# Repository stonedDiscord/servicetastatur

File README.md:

# Servicetastatur

Ein Nachbau der Servicetastatur für Merkur Geräte ab Profitech 3000.

Man kann diese bei Auftragsfertigern bauen lassen,
EPROM, CPU, Display und Gehäuse müssen seperat beschafft werden.

Gehäuse ist [in Arbeit](https://github.com/stonedDiscord/servicetastatur/blob/master/case.scad),
es werden die Bibliotheken [jl_scad](https://github.com/lijon/jl_scad) und [BOSL2](https://github.com/BelfrySCAD/BOSL2) benötigt.

## Lizenz

Nachbauen und Modifizieren durch Dritte ist erlaubt, die Dokumentation inkl Schaltplan und Gerber müssen aber mit weitergegeben werden.
Die Lizenz gibt es hier auf Deutsch
https://creativecommons.org/licenses/by-sa/4.0/deed.de

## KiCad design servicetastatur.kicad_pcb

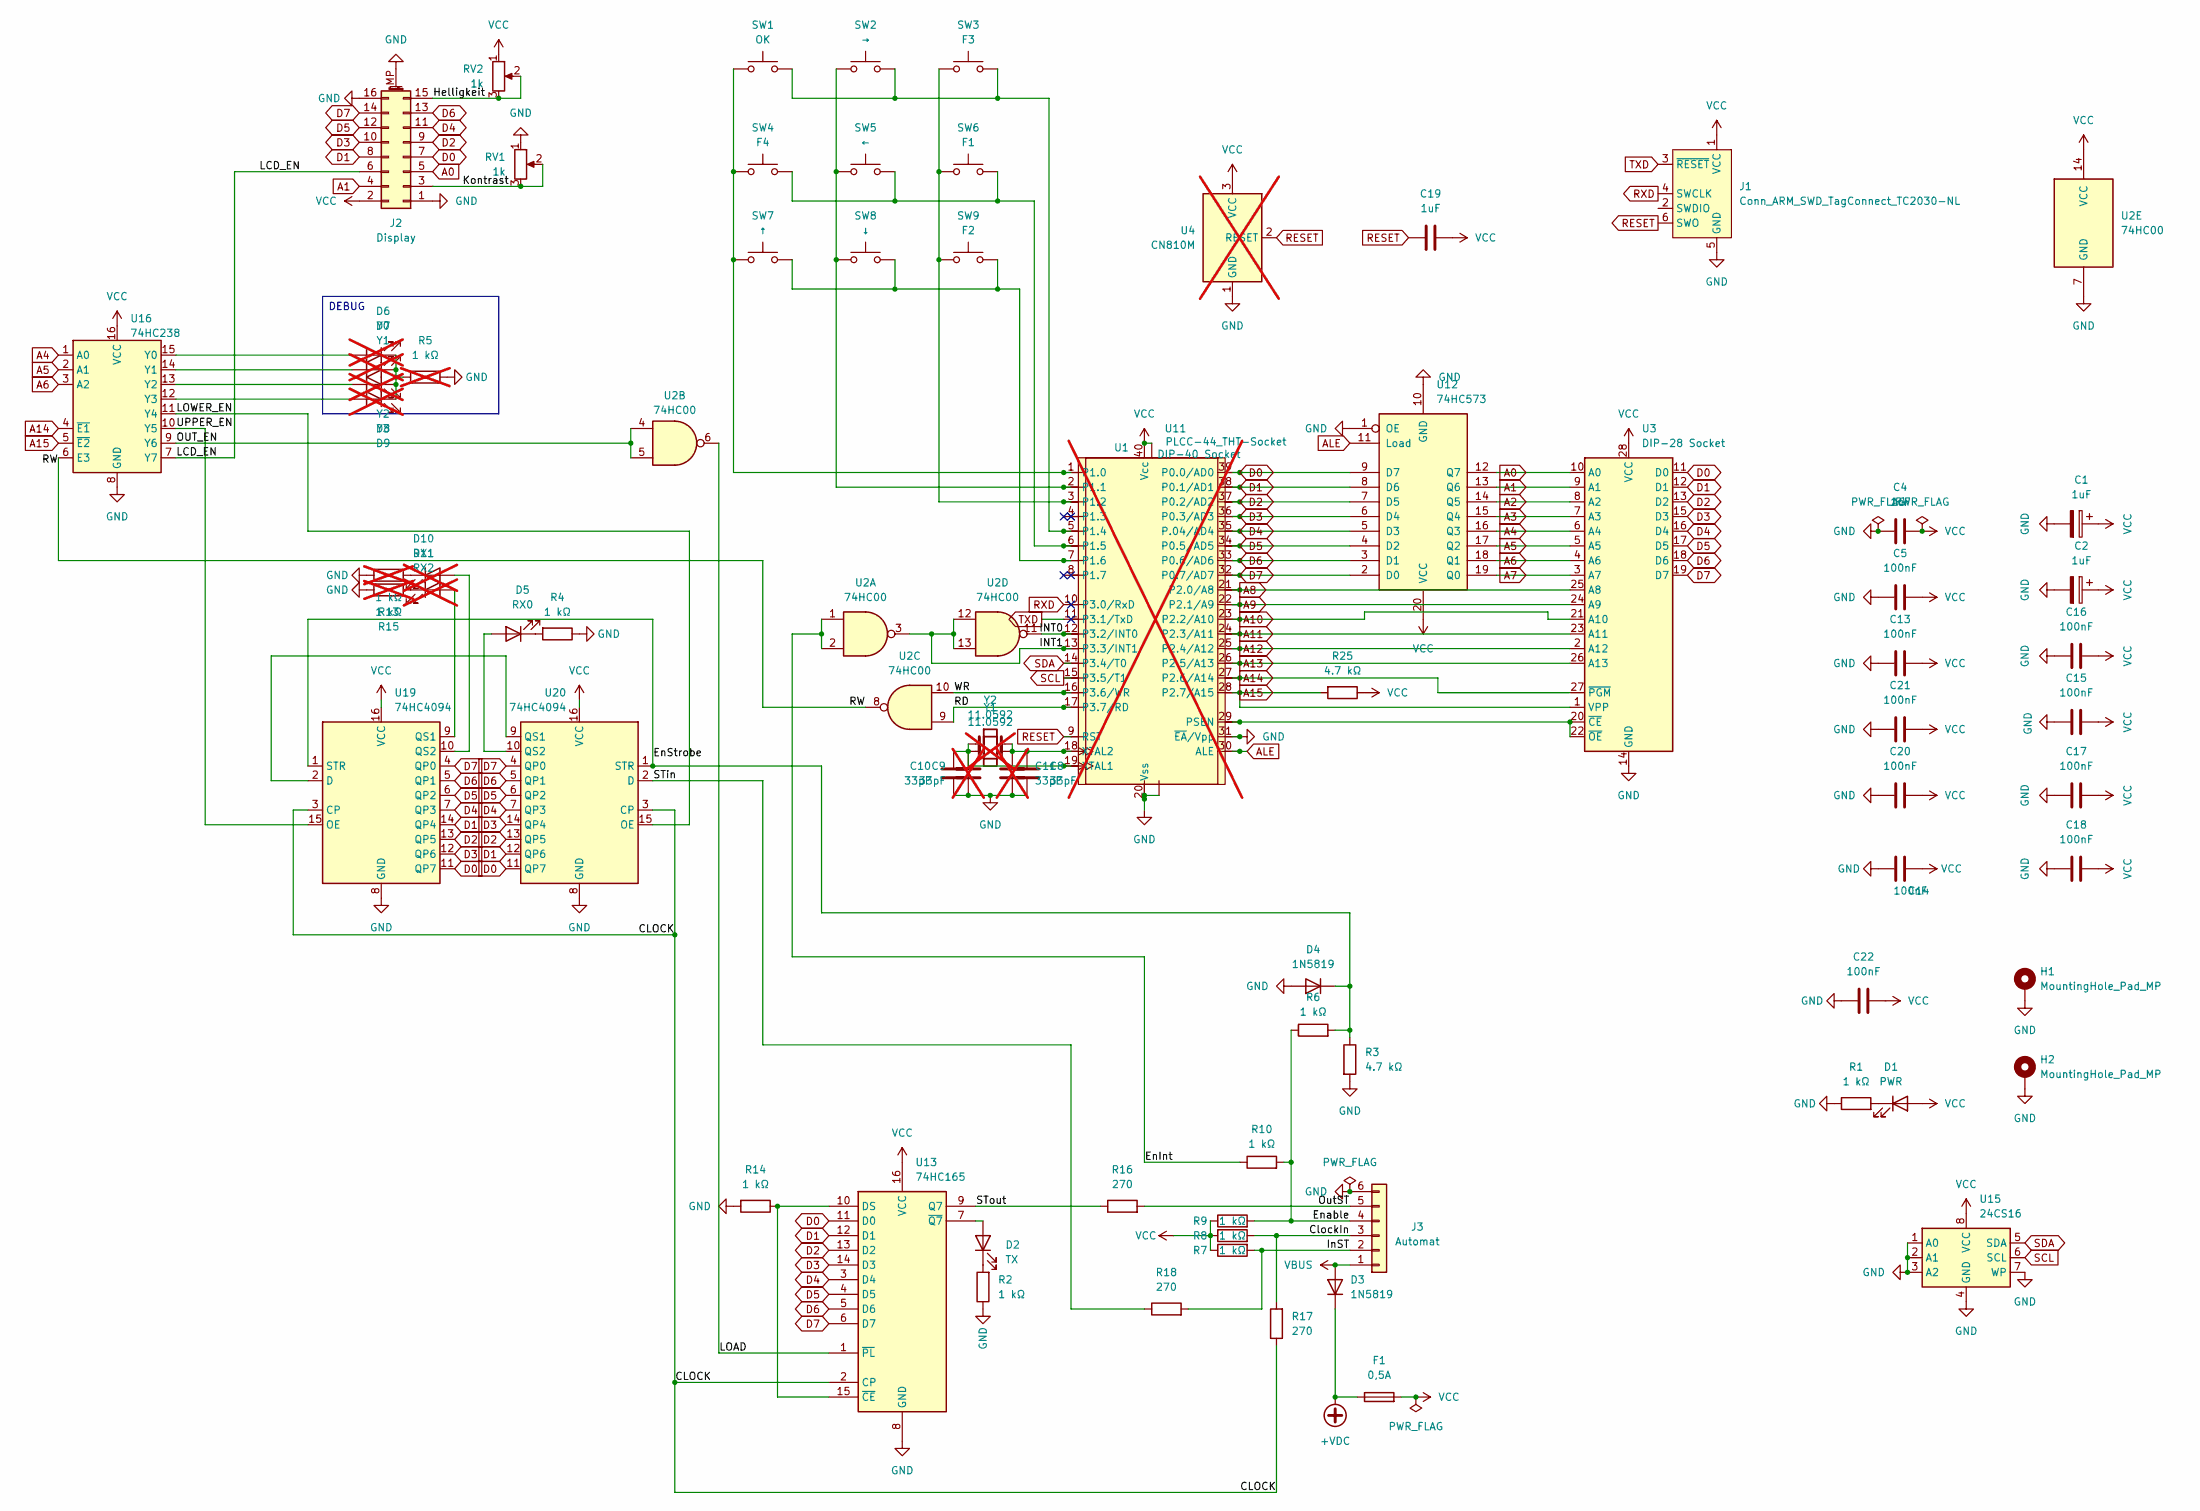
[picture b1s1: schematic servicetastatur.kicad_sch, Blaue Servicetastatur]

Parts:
C1, C2, C4, C19: 1uF; C_1206_3216Metric
C5, C13, C14, C15, C16, C17, C18, C20, C21, C22: 100nF; C_0603_1608Metric
C8, C10: 33pF; C_0603_1608Metric
C9, C11: 33pF; C_0603_1608Metric; not fitted
D1: PWR; LED_0805_2012Metric
D2: TX; LED_0805_2012Metric
D3, D4: 1N5819; D_SOD-123
D5: RX0; LED_0805_2012Metric
D6: Y0; LED_0805_2012Metric; not fitted
D7: Y1; LED_0805_2012Metric; not fitted
D8: Y2; LED_0805_2012Metric; not fitted
D9: Y3; LED_0805_2012Metric; not fitted
D10: RX1; LED_0805_2012Metric; not fitted
D11: RX2; LED_0805_2012Metric; not fitted
F1: 0,5A; Fuse_0805_2012Metric
H1, H2: MountingHole_Pad_MP; MountingHole 3.5mm
J1: Conn_ARM_SWD_TagConnect_TC2030-NL; Tag-Connect_TC2030-IDC-NL_2x03_P1.27mm_Vertical
J2: Display; LCDdisplay
J3: Automat; Conn01x06
R1, R2, R4, R6, R7, R8, R9, R10, R14: 1 kΩ; R_0603_1608Metric
R3, R25: 4.7 kΩ; R_0603_1608Metric
R5, R13, R15: 1 kΩ; R_0603_1608Metric; not fitted
R16, R17, R18: 270; R_0603_1608Metric
RV1, RV2: 1k; Potentiometer_Piher_PT-6-V_Vertical_Hole
SW1: OK; SW_Push_1P1T_XKB_TS-1187A
SW2: →; SW_Push_1P1T_XKB_TS-1187A
SW3: F3; SW_Push_1P1T_XKB_TS-1187A
SW4: F4; SW_Push_1P1T_XKB_TS-1187A
SW5: ←; SW_Push_1P1T_XKB_TS-1187A
SW6: F1; SW_Push_1P1T_XKB_TS-1187A
SW7: ↑; SW_Push_1P1T_XKB_TS-1187A
SW8: ↓; SW_Push_1P1T_XKB_TS-1187A
SW9: F2; SW_Push_1P1T_XKB_TS-1187A
U1: DIP-40 Socket; DIP-40_W15.24mm
U2: 74HC00; SOIC-14_3.9x8.7mm_P1.27mm
U3: DIP-28 Socket; DIP-28_W15.24mm
U4: CN810M; SOT-23; not fitted
U11: PLCC-44_THT-Socket; not fitted
U12: 74HC573; TSSOP-20_4.4x6.5mm_P0.65mm
U13: 74HC165; SOP-16_4.4x10.4mm_P1.27mm
U15: 24CS16; SO-8_3.9x4.9mm_P1.27mm
U16: 74HC238; SOIC-16W_5.3x10.2mm_P1.27mm
U19, U20: 74HC4094; SOIC-16W_5.3x10.2mm_P1.27mm
Y1: 11.0592; Crystal_HC49-U_Vertical; not fitted
Y2: 11.0592; Crystal_SMD_HC49-SD

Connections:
+VDC: D3.1 (K), F1.1
/CLOCK: R17.1, U13.2 (CP), U19.3 (CP), U20.3 (CP)
/ClockIn: J3.3, R8.2, R17.2
/EnInt: R10.1, U2.1, U2.2
/EnStrobe: D4.1 (K), R3.1, R6.2, U19.1 (STR), U20.1 (STR)
/Enable: J3.4, R6.1, R9.2, R10.2
/Helligkeit: J2.15, RV2.2, RV2.3
/INT0: U1.12 (P3.2/INT0), U2.11, U11.14 (P3.2/INT0)
/INT1: U1.13 (P3.3/INT1), U2.3, U2.12, U2.13, U11.15 (P3.3/INT1)
/InST: J3.2, R7.2, R18.2
/Kontrast: J2.3, RV1.2, RV1.3
/LCD_EN: J2.6, U16.7 (Y7)
/LOAD: U2.6, U13.1 (~PL)
/LOWER_EN: U16.11 (Y4), U20.15 (OE)
/OUT_EN: U2.4, U2.5, U16.9 (Y6)
/OutST: J3.5, R16.2
/RD: U1.17 (P3.7/RD), U2.9, U11.19 (P3.7/RD)
/RW: U2.8, U16.6 (E3)
/STin: R18.1, U20.2 (D)
/STout: R16.1, U13.9 (Q7)
/UPPER_EN: U16.10 (Y5), U19.15 (OE)
/WR: U1.16 (P3.6/WR), U2.10, U11.18 (P3.6/WR)
A0: J2.5, U3.10 (A0), U12.12 (Q7)
A1: J2.4, U3.9 (A1), U12.13 (Q6)
A2: U3.8 (A2), U12.14 (Q5)
A3: U3.7 (A3), U12.15 (Q4)
A4: U3.6 (A4), U12.16 (Q3), U16.1 (A0)
A5: U3.5 (A5), U12.17 (Q2), U16.2 (A1)
A6: U3.4 (A6), U12.18 (Q1), U16.3 (A2)
A7: U3.3 (A7), U12.19 (Q0)
A8: U1.21 (P2.0/A8), U3.25 (A8), U11.24 (P2.0/A8)
A9: U1.22 (P2.1/A9), U3.24 (A9), U11.25 (P2.1/A9)
A10: U1.23 (P2.2/A10), U3.21 (A10), U11.26 (P2.2/A10)
A11: U1.24 (P2.3/A11), U3.23 (A11), U11.27 (P2.3/A11)
A12: U1.25 (P2.4/A12), U3.2 (A12), U11.28 (P2.4/A12)
A13: U1.26 (P2.5/A13), U3.26 (A13), U11.29 (P2.5/A13)
A14: U1.27 (P2.6/A14), U3.27 (~PGM), U11.30 (P2.6/A14), U16.4 (~E1)
A15: R25.2, U1.28 (P2.7/A15), U3.1 (VPP), U11.31 (P2.7/A15), U11.34 (NIC), U16.5 (~E2)
ALE: U1.30 (ALE), U11.33 (ALE), U12.11 (Load)
D0: J2.7, U1.39 (P0.0/AD0), U3.11 (D0), U11.43 (P0.0/AD0), U12.9 (D7), U13.11 (D0), U19.11 (QP7), U20.11 (QP7)
D1: J2.8, U1.38 (P0.1/AD1), U3.12 (D1), U11.42 (P0.1/AD1), U12.8 (D6), U13.12 (D1), U19.14 (QP4), U20.12 (QP6)
D2: J2.9, U1.37 (P0.2/AD2), U3.13 (D2), U11.41 (P0.2/AD2), U12.7 (D5), U13.13 (D2), U19.13 (QP5), U20.13 (QP5)
D3: J2.10, U1.36 (P0.3/AD3), U3.15 (D3), U11.40 (P0.3/AD3), U12.6 (D4), U13.14 (D3), U19.12 (QP6), U20.14 (QP4)
D4: J2.11, U1.35 (P.04/AD4), U3.16 (D4), U11.39 (P.04/AD4), U12.5 (D3), U13.3 (D4), U19.7 (QP3), U20.7 (QP3)
D5: J2.12, U1.34 (P0.5/AD5), U3.17 (D5), U11.38 (P0.5/AD5), U12.4 (D2), U13.4 (D5), U19.6 (QP2), U20.6 (QP2)
D6: J2.13, U1.33 (P0.6/AD6), U3.18 (D6), U11.37 (P0.6/AD6), U12.3 (D1), U13.5 (D6), U19.5 (QP1), U20.5 (QP1)
D7: J2.14, U1.32 (P0.7/AD7), U3.19 (D7), U11.36 (P0.7/AD7), U12.2 (D0), U13.6 (D7), U19.4 (QP0), U20.4 (QP0)
GND: C1.2, C2.2, C4.1, C5.1, C8.1, C9.1, C10.1, C11.1, C13.1, C14.2, C15.1, C16.1, C17.1, C18.1, C20.2, C21.2, C22.1, D4.2 (A), H1.MP, H2.MP, J1.5 (GND), J2.1, J2.16, J2.MP (MountPin), J3.6, R1.1, R2.1, R3.2, R4.1, R5.1, R13.1, R14.2, R15.1, RV1.1, U1.20 (Vss), U1.31 (~EA/Vpp), U2.7 (GND), U3.14 (GND), U4.1 (GND), U11.1 (Vss1), U11.22 (Vss), U11.35 (EA), U12.1 (OE), U12.10 (GND), U13.8 (GND), U15.1 (A0), U15.2 (A1), U15.3 (A2), U15.4 (GND), U15.7 (WP), U16.8 (GND), U19.8 (GND), U20.8 (GND)
unnamed: D1.1 (K), R1.2
unnamed: D2.2 (A), U13.7 (~Q7)
unnamed: D2.1 (K), R2.2
unnamed: D5.2 (A), U20.10 (QS2)
unnamed: D5.1 (K), R4.2
unnamed: D6.2 (A), U16.15 (Y0)
unnamed: D6.1 (K), D7.1 (K), D8.1 (K), D9.1 (K), R5.2
unnamed: D7.2 (A), U16.14 (Y1)
unnamed: D8.2 (A), U16.13 (Y2)
unnamed: D9.2 (A), U16.12 (Y3)
unnamed: D10.2 (A), U19.10 (QS2)
unnamed: D10.1 (K), R13.2
unnamed: D11.2 (A), U19.9 (QS1)
unnamed: D11.1 (K), R15.2
unnamed: SW1.1, SW4.1, SW7.1, U1.1 (P1.0), U11.2 (P1.0)
unnamed: SW2.1, SW5.1, SW8.1, U1.2 (P1.1), U11.3 (P1.1)
unnamed: SW3.1, SW6.1, SW9.1, U1.3 (P1.2), U11.4 (P1.2)
unnamed: SW1.2, SW2.2, SW3.2, U1.5 (P1.4), U11.6 (P1.4)
unnamed: SW4.2, SW5.2, SW6.2, U1.6 (P1.5), U11.7 (P1.5)
unnamed: SW7.2, SW8.2, SW9.2, U1.7 (P1.6), U11.8 (P1.6)
unnamed: U1.29 (PSEN), U3.20 (~CE), U3.22 (~OE), U11.32 (PSEN)
unnamed: C9.2, C10.2, U1.19 (XTAL1), U11.21 (XTAL1), Y1.1, Y2.1
unnamed: C8.2, C11.2, U1.18 (XTAL2), U11.20 (XTAL2), Y1.2, Y2.2
unnamed: R14.1, U13.10 (DS), U13.15 (~CE)
unnamed: U19.2 (D), U20.9 (QS1)
RESET: C19.1, J1.6 (SWO), U1.9 (RST), U4.2 (RESET), U11.10 (RST)
RXD: J1.4 (SWCLK), U1.10 (P3.0/RxD)
SCL: U1.15 (P3.5/T1), U11.17 (P3.5/T1), U15.6 (SCL)
SDA: U1.14 (P3.4/T0), U11.16 (P3.4/T0), U15.5 (SDA)
TXD: J1.3 (~RESET), U1.11 (P3.1/TxD)
VBUS: D3.2 (A), J3.1
VCC: C1.1, C2.1, C4.2, C5.2, C13.2, C14.1, C15.2, C16.2, C17.2, C18.2, C19.2, C20.1, C21.1, C22.2, D1.2 (A), F1.2, J1.1 (VCC), J2.2, R7.1, R8.1, R9.1, R25.1, RV2.1, U1.40 (Vcc), U2.14 (VCC), U3.28 (VCC), U4.3 (VCC), U11.44 (Vcc), U12.20 (VCC), U13.16 (VCC), U15.8 (VCC), U16.16 (VCC), U19.16 (VCC), U20.16 (VCC)

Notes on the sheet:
DEBUG

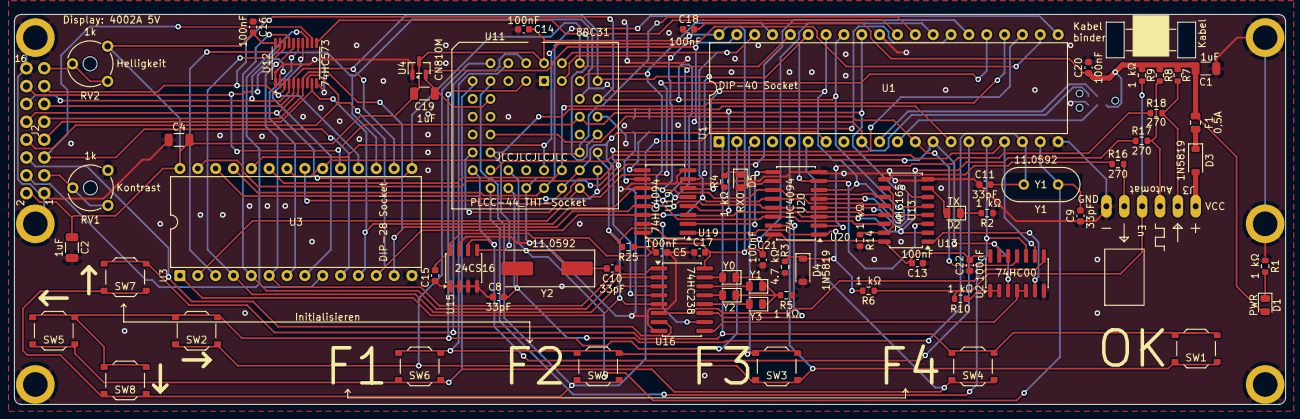
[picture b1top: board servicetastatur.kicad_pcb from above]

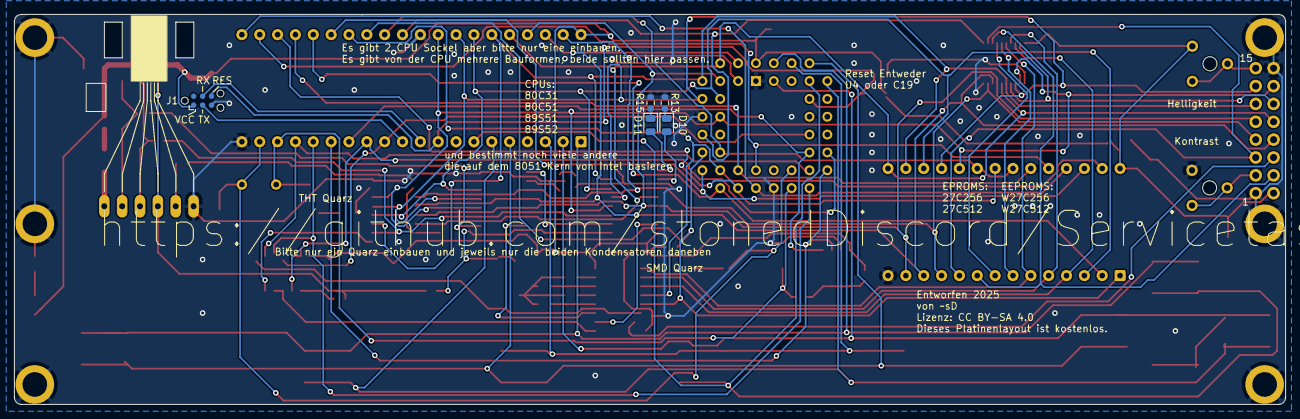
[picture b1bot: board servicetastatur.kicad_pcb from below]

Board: 2 copper layers, 180.9 x 55.5 mm, 76 parts (5 on the bottom side), 80 nets.

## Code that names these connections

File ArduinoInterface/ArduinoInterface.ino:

// Servicetastatur-Interface
// J3 (top to bottom): VBUS - InST - ClockIn - Enable - STout - GND
// TX (Board to Machine): U13 74HC165 (8-bit PISO, no swap, no pin reversal)
// RX (Machine to Board): U20+U19 74HC4094 Cascade (16-bit SIPO, swap D1/D3 on U19, pins reversed QP7=D0)

const int PIN_TX  = 5;  // Arduino Output: InST / 2STin at U20 (Board RX)
const int PIN_EN  = 2;  // Arduino Input: EnStrobe from machine (INT0)
const int PIN_CLK = 3;  // Arduino Input: Clock from machine (INT1)
const int PIN_RX  = 4;  // Arduino Input: STout from U13 (Board TX)

// TX from board perspective (sniffed by Arduino from U13)
volatile uint16_t txShift   = 0;
volatile uint16_t txLatched = 0;
volatile bool     txReady   = false;

// RX from board perspective (driven by Arduino into U20/U19)
volatile uint16_t rxData   = 0x0000;
volatile int8_t   rxBitPos = 15;

// Helper to reverse bits in a byte
uint8_t reverseByte(uint8_t x) {
  x = ((x & 0x55) << 1) | ((x & 0xAA) >> 1);
  x = ((x & 0x33) << 2) | ((x & 0xCC) >> 2);
  x = (x << 4) | (x >> 4);
  return x;
}

// Process data transmitted by the board (from U13)
uint8_t processTX(uint16_t val) {
  // U13 has no swap and no reversal.
  // After 16 clocks (MSB first), the 8 bits of data end up in the upper byte.
  return (uint8_t)((val >> 8) & 0xFF);
}

// Prepare data for the board to receive (into U19/U20)
uint16_t prepareRX(uint16_t val) {
  uint8_t low  = val & 0xFF;
  uint8_t high = (val >> 8) & 0xFF;

  // 1. D1 and D3 are swapped on U19 (RX path)
  uint8_t d1 = (low >> 1) & 1;
  uint8_t d3 = (low >> 3) & 1;
  low &= ~((1 << 1) | (1 << 3));
  low |= (d3 << 1) | (d1 << 3);

  // 2. Pins are reversed on U19/U20 (QP7=D0)
  low  = reverseByte(low);
  high = reverseByte(high);

  // U19 (low byte) is at the end of the shift chain.
  // Bits are shifted MSB first (bit 15 down to 0).
  // The first 8 bits shifted end up in U19, the next 8 in U20.
  return ((uint16_t)low << 8) | high;
}

void isr_clock() {
  if (digitalRead(PIN_CLK) == HIGH) {
    // Rising edge: read Board TX bit, advance Board RX bit pointer
    txShift = (txShift << 1) | (uint16_t)digitalRead(PIN_RX);
    if (rxBitPos > 0) rxBitPos--;
  } else {
    // Falling edge: output next Board RX bit (stable before next rising edge)
    digitalWrite(PIN_TX, (rxData >> rxBitPos) & 1);
  }
}

void isr_enable() {
  // Rising edge: secure TX frame, reset RX and TX for next frame
  txLatched = txShift;
  txReady   = true;
  txShift   = 0;
  rxBitPos  = 15;
  digitalWrite(PIN_TX, (rxData >> 15) & 1);
}

void setup() {
  Serial.begin(115200);
  pinMode(PIN_TX,  OUTPUT);
  pinMode(PIN_EN,  INPUT);
  pinMode(PIN_CLK, INPUT);
  pinMode(PIN_RX,  INPUT);
  digitalWrite(PIN_TX, (rxData >> 15) & 1);
  attachInterrupt(digitalPinToInterrupt(PIN_EN),  isr_enable, RISING);
  attachInterrupt(digitalPinToInterrupt(PIN_CLK), isr_clock,  CHANGE);
}

void loop() {
  if (txReady) {
    noInterrupts();
    uint16_t val = txLatched;
    txReady = false;
    interrupts();

    // Extract raw byte from Board TX stream
    uint8_t txValue = processTX(val);

    Serial.print("TX: 0x");
    if (txValue < 0x10) Serial.print("0");
    Serial.println(txValue, HEX);
  }

  // Receive hex value via Serial to send to Board RX, e.g. "A5"
  if (Serial.available()) {
    String s = Serial.readStringUntil('\n');
    s.trim();
    if (s.length() > 0) {
      uint16_t val  = (uint16_t)strtoul(s.c_str(), nullptr, 16);
      uint16_t prepared = prepareRX(val);
      noInterrupts();
      rxData   = prepared;
      rxBitPos = 15;
      digitalWrite(PIN_TX, (rxData >> 15) & 1);
      interrupts();
      Serial.print("RX: 0x");
      Serial.print(val, HEX);
      Serial.print(" -> prepared: 0x");
      Serial.println(prepared, HEX);
    }
  }
}

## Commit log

2023-09-06 krumm
2023-09-06 oops kibot vergessen
2023-09-06 fix photo
2023-09-06 rand
2023-09-06 kein skaliern
2023-09-06 fuck
2023-09-06 kleiner
2023-09-06 war nochmal kleiner
2023-09-06 wieder groesser
2023-09-06 groesse
2023-09-06 neue fotos
2023-09-06 rumgeschiebe
2023-09-06 anschluss
2023-09-06 elkos gedreht
2023-09-06 i mag ned mehr
2023-09-12 gross
2023-09-12 sdfsdf
2024-01-18 loin
2024-10-07 2024 update
2024-10-07 caps
2024-10-07 shift register
2024-10-15 stecker
2024-10-19 spekulation
2024-11-06 bilder
2024-11-06 footprints
2024-11-06 layout
2024-11-08 so hab bestellt
2024-11-20 deko
2024-11-29 CC BY-SA 4.0
2025-02-09 lcd gefixt
2025-03-11 4002A display
2025-03-11 dip 80c31
2025-03-11 kompakt
2025-03-11 replace reset circuit with cap
2025-03-15 bestellt 2
2025-03-30 kontrast gnd
2025-03-31 0603
2025-05-02 linguist override
2025-05-19 reset chip
2025-07-09 pin names
2025-09-07 test
2025-11-02 clock
2025-11-09 testprogramm
2025-11-09 deckel
2025-12-18 kibot template
2025-12-18 schematic kibot file
2025-12-18 kibot
2025-12-18 sdcc build
2025-12-18 valid bin
2025-12-18 try this docker step
2025-12-18 path
2025-12-18 screw docker
2025-12-18 cache
2025-12-18 wrong package
2025-12-18 rename to firmware
2025-12-18 documentatione
2025-12-18 display header
2025-12-18 line defs
2026-01-06 2026 update
2026-01-06 keypad scan
2026-01-06 mein foto
2026-01-06 rename var
2026-01-06 return function
2026-01-06 ignore builds
2026-01-07 wrong comments
2026-01-07 lines
2026-01-07 interrupts
2026-01-07 int handler
2026-01-07 led blink
2026-01-08 addr
2026-01-08 arduino test
2026-01-08 remove nc
2026-01-09 richtungen
2026-01-09 buttons
2026-01-09 wand
2026-01-10 rotate
2026-01-10 test script
2026-01-17 case
2026-01-17 header
2026-01-17 prep
2026-01-17 guides
2026-01-23 debug led
2026-01-23 pad burn
2026-01-23 hole
2026-01-25 broken
2026-01-25 etwas
2026-01-25 break
2026-01-25 rage
2026-01-25 experiment
2026-01-25 lcsc
2026-02-06 pio skelet
2026-02-06 pio header
2026-02-06 hex path
2026-02-07 gitignore vscode
2026-02-07 tester geht
2026-02-07 weg vom crystal
2026-02-07 inpin
2026-02-07 set up project for pio
2026-02-07 arduino framework
2026-02-07 arduino header and move to cpp
2026-02-07 Squashed commit of the following:
    commit 8158f11a7876317cc5d9a1b01b5ff45f2dccbbc1
    Author: stonedDiscord <Tukz@gmx.de>
    Date: Sat Feb 7 17:56:19 2026 +0100
    arduino header and move to cpp
    commit 4ade06e093e7fc0500cbfabf0a8437dced51609a
    Author: stonedDiscord <Tukz@gmx.de>
2026-02-07 data out
2026-02-08 keine nullen
2026-03-10 copy libraries
2026-03-10 halbe
2026-03-10 haelfte
2026-03-10 artifact
2026-03-10 render folder
2026-03-10 names
2026-03-10 every push
2026-03-10 artifact names
2026-03-10 no stl
2026-03-10 release
2026-03-10 you have one job
2026-03-10 gerb
2026-03-10 gerber
2026-03-10 gerberdir
2026-03-10 ext memory
2026-03-10 move gitignore
2026-03-10 switch to stc
2026-03-10 taster
2026-03-10 hide plcc pins
2026-03-10 embed perms
2026-03-10 pio tester
2026-03-10 symbol and tester
2026-03-10 tag connect
2026-03-10 keep zip
2026-03-10 direction names
2026-03-10 pio subfolders
2026-03-10 taster tab
2026-03-10 dont
2026-03-10 case lib
2026-03-10 commands
2026-03-10 zips are in subfolders
2026-03-10 commented out
2026-04-01 suggest platformio instead of cpp
2026-04-01 add vscode workspace for platformio detection
2026-04-01 fix platformio warning
2026-04-07 move resets
2026-04-07 2 solutions 1 problem
2026-05-01 swapperoo
2026-05-01 strings
2026-05-01 keyc
2026-05-01 lookup
2026-05-01 lcd range
2026-05-22 all folders

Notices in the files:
servicetastatur.kicad_pcb:
Lizenz: CC BY-SA 4.0
